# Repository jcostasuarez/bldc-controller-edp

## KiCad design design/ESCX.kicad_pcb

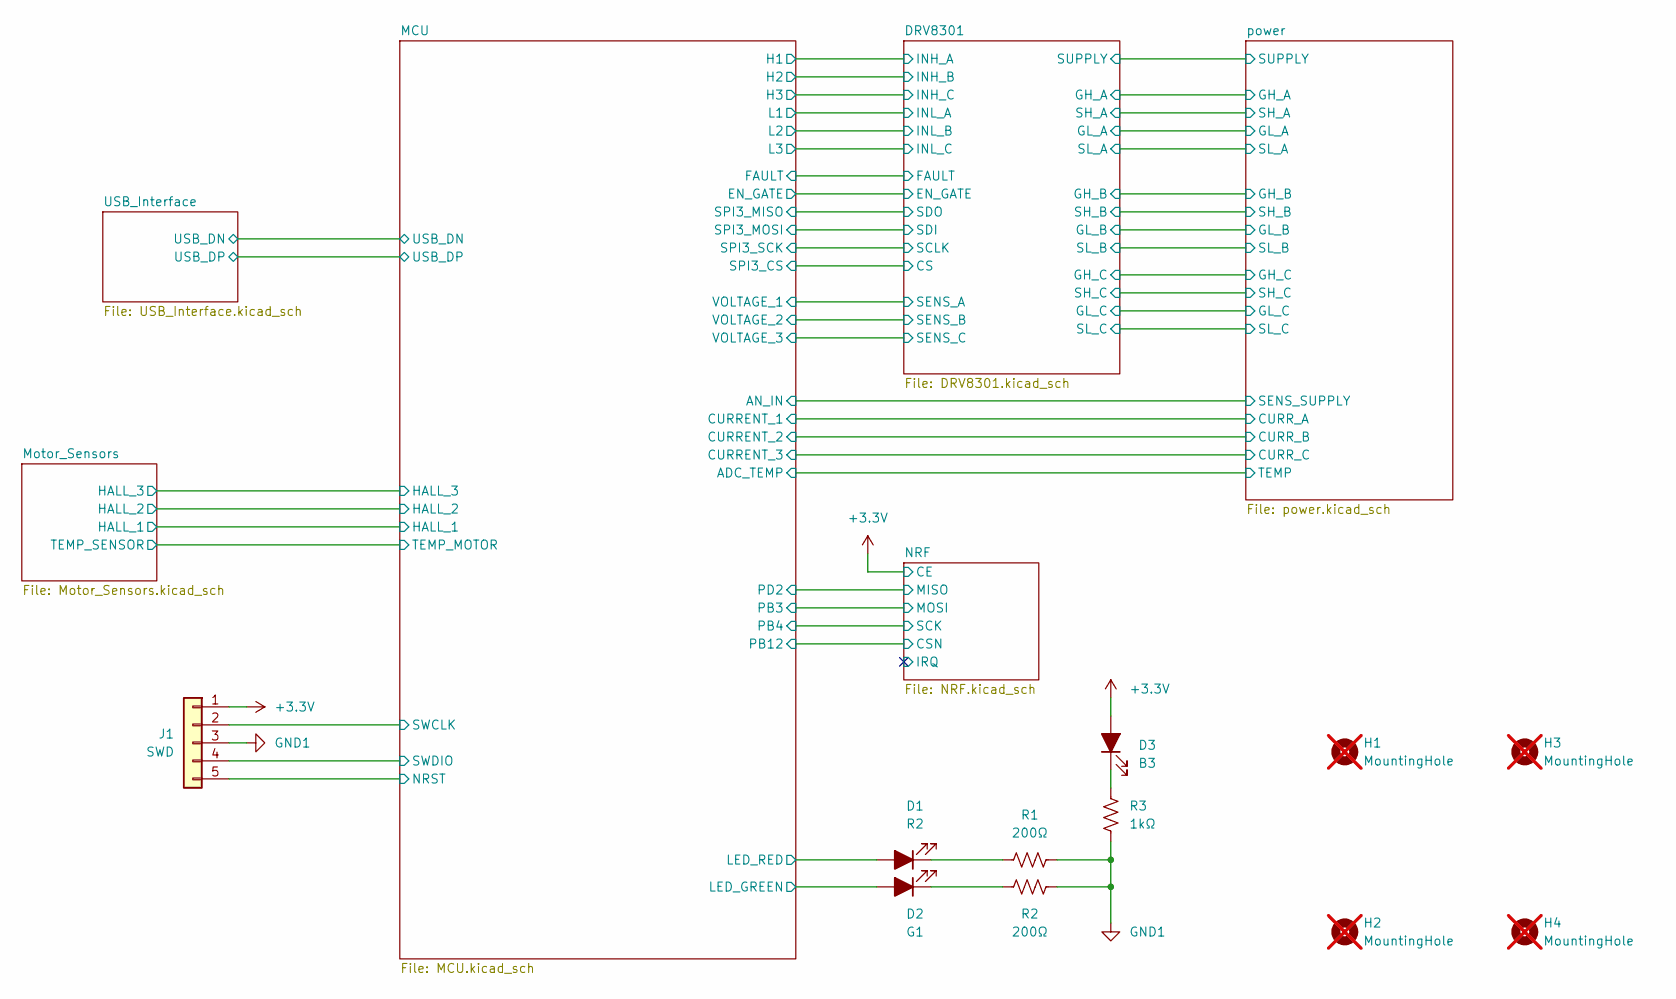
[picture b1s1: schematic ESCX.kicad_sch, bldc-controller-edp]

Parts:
D1: R2; LED_0603_1608Metric; LCSC C2286
D2: G1; LED_0603_1608Metric; LCSC C2286
D3: B3; LED_0603_1608Metric; LCSC C2286
H1, H2, H3, H4: MountingHole; MountingHole_2.7mm_M2.5; not fitted
J1: SWD; PinHeader_1x05_P2.54mm_Vertical; LCSC C6332198
R1, R2: 200Ω; R_0603_1608Metric; LCSC C8218
R3: 1kΩ; R_0603_1608Metric; LCSC C21190

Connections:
+3.3V: D3.2 (A), J1.1; also elsewhere on the board
/MCU/LED_GREEN: D2.2 (A); also elsewhere on the board
/MCU/LED_RED: D1.2 (A); also elsewhere on the board
/MCU/NRST: J1.5; also elsewhere on the board
/MCU/SWCLK: J1.2; also elsewhere on the board
/MCU/SWDIO: J1.4; also elsewhere on the board
GND1: J1.3, R1.2, R2.2, R3.1; also elsewhere on the board
unnamed: D1.1 (K), R1.1
unnamed: D2.1 (K), R2.1
unnamed: D3.1 (K), R3.2

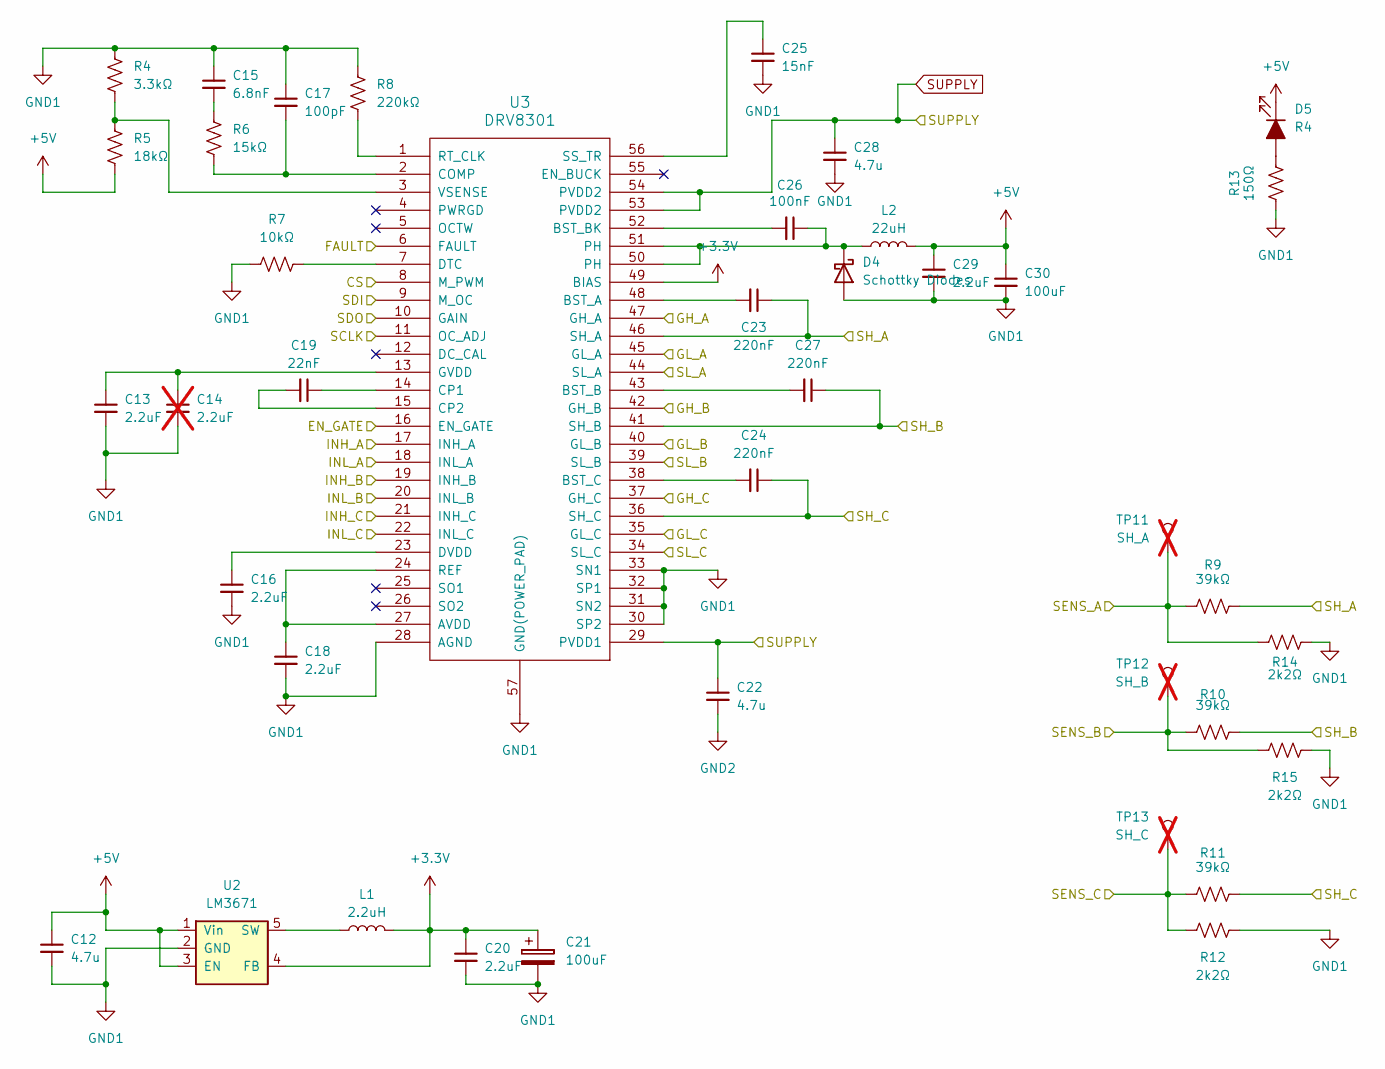
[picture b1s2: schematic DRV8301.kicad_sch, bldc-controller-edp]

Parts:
C12: 4.7u; C_0603_1608Metric; LCSC C19666
C13, C16, C18, C20, C29: 2.2uF; C_0603_1608Metric; LCSC C23630
C14: 2.2uF; C_0603_1608Metric; not fitted
C15: 6.8nF; C_0603_1608Metric; LCSC C1631
C17: 100pF; C_0603_1608Metric; LCSC C14858
C19: 22nF; C_0603_1608Metric; LCSC C21122
C21, C30: 100uF; C_1206_3216Metric; LCSC C15008
C22, C28: 4.7u; C_1210_3225Metric; LCSC C337978
C23, C24, C27: 220nF; C_0603_1608Metric; LCSC C21120
C25: 15nF; C_0603_1608Metric; LCSC C113809
C26: 100nF; C_0603_1608Metric; LCSC C14663
D4: Schottky Diodes; D_SMA; LCSC C22452
D5: R4; LED_0603_1608Metric; LCSC C2286
L1: 2.2uH; L_0603_1608Metric; LCSC C18221249
L2: 22uH; L_0603_1608Metric_Pad1.05x0.95mm_HandSolder; LCSC C6808015
R4: 3.3kΩ; R_0603_1608Metric; LCSC C22978
R5: 18kΩ; R_0603_1608Metric; LCSC C25810
R6: 15kΩ; R_0603_1608Metric; LCSC C22809
R7: 10kΩ; R_0603_1608Metric; LCSC C25804
R8: 220kΩ; R_0603_1608Metric; LCSC C22961
R9, R10, R11: 39kΩ; R_0603_1608Metric; LCSC C23153
R12, R14, R15: 2k2Ω; R_0603_1608Metric; LCSC C4190
R13: 150Ω; R_0603_1608Metric; LCSC C22808
TP11: SH_A; PinHeader_1x01_P2.54mm_Vertical; not fitted
TP12: SH_B; PinHeader_1x01_P2.54mm_Vertical; not fitted
TP13: SH_C; PinHeader_1x01_P2.54mm_Vertical; not fitted
U2: LM3671; MF05A; LCSC C2650333
U3: DRV8301; HTSSOP-56-1EP_6.1x14mm_P0.5mm_EP3.61x6.35mm; LCSC C98969

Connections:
+3.3V: C20.1, C21.1, L1.2, U2.4 (FB), U3.49 (BIAS); also elsewhere on the board
+5V: C12.1, C29.1, C30.1, D5.1 (K), L2.2, R5.2, U2.1 (Vin), U2.3 (EN); also elsewhere on the board
/DRV8301/CS: U3.8 (M_PWM); also elsewhere on the board
/DRV8301/EN_GATE: U3.16 (EN_GATE); also elsewhere on the board
/DRV8301/FAULT: U3.6 (FAULT); also elsewhere on the board
/DRV8301/GH_A: U3.47 (GH_A); also elsewhere on the board
/DRV8301/GH_B: U3.42 (GH_B); also elsewhere on the board
/DRV8301/GH_C: U3.37 (GH_C); also elsewhere on the board
/DRV8301/GL_A: U3.45 (GL_A); also elsewhere on the board
/DRV8301/GL_B: U3.40 (GL_B); also elsewhere on the board
/DRV8301/GL_C: U3.35 (GL_C); also elsewhere on the board
/DRV8301/INH_A: U3.17 (INH_A); also elsewhere on the board
/DRV8301/INH_B: U3.19 (INH_B); also elsewhere on the board
/DRV8301/INH_C: U3.21 (INH_C); also elsewhere on the board
/DRV8301/INL_A: U3.18 (INL_A); also elsewhere on the board
/DRV8301/INL_B: U3.20 (INL_B); also elsewhere on the board
/DRV8301/INL_C: U3.22 (INL_C); also elsewhere on the board
/DRV8301/SCLK: U3.11 (OC_ADJ); also elsewhere on the board
/DRV8301/SDI: U3.9 (M_OC); also elsewhere on the board
/DRV8301/SDO: U3.10 (GAIN); also elsewhere on the board
/DRV8301/SENS_A: R9.2, R14.2, TP11.1; also elsewhere on the board
/DRV8301/SENS_B: R10.2, R15.2, TP12.1; also elsewhere on the board
/DRV8301/SENS_C: R11.2, R12.2, TP13.1; also elsewhere on the board
/DRV8301/SH_A: C23.1, R9.1, U3.46 (SH_A); also elsewhere on the board
/DRV8301/SH_B: C27.1, R10.1, U3.41 (SH_B); also elsewhere on the board
/DRV8301/SH_C: C24.1, R11.1, U3.36 (SH_C); also elsewhere on the board
/DRV8301/SL_A: U3.44 (SL_A); also elsewhere on the board
/DRV8301/SL_B: U3.39 (SL_B); also elsewhere on the board
/DRV8301/SL_C: U3.34 (SL_C); also elsewhere on the board
GND1: C12.2, C13.2, C14.2, C15.1, C16.2, C17.1, C18.2, C20.2, C21.2, C25.2, C28.2, C29.2, C30.2, D4.2 (A), R4.1, R7.2, R8.1, R12.1, R13.2, R14.1, R15.1, U2.2 (GND), U3.28 (AGND), U3.30 (SP2), U3.31 (SN2), U3.32 (SP1), U3.33 (SN1), U3.57 (GND(POWER_PAD)); also elsewhere on the board
GND2: C22.2; also elsewhere on the board
unnamed: C15.2, R6.1
unnamed: C26.1, D4.1 (K), L2.1, U3.50 (PH), U3.51 (PH)
unnamed: D5.2 (A), R13.1
unnamed: L1.1, U2.5 (SW)
unnamed: C18.1, U3.24 (REF), U3.27 (AVDD)
unnamed: C23.2, U3.48 (BST_A)
unnamed: C27.2, U3.43 (BST_B)
unnamed: C26.2, U3.52 (BST_BK)
unnamed: C24.2, U3.38 (BST_C)
unnamed: C17.2, R6.2, U3.2 (COMP)
unnamed: C19.1, U3.14 (CP1)
unnamed: C19.2, U3.15 (CP2)
unnamed: R7.1, U3.7 (DTC)
unnamed: C16.1, U3.23 (DVDD)
unnamed: C13.1, C14.1, U3.13 (GVDD)
unnamed: R8.2, U3.1 (RT_CLK)
unnamed: C25.1, U3.56 (SS_TR)
unnamed: R4.2, R5.1, U3.3 (VSENSE)
SUPPLY: C22.1, C28.1, U3.29 (PVDD1), U3.53 (PVDD2), U3.54 (PVDD2); also elsewhere on the board

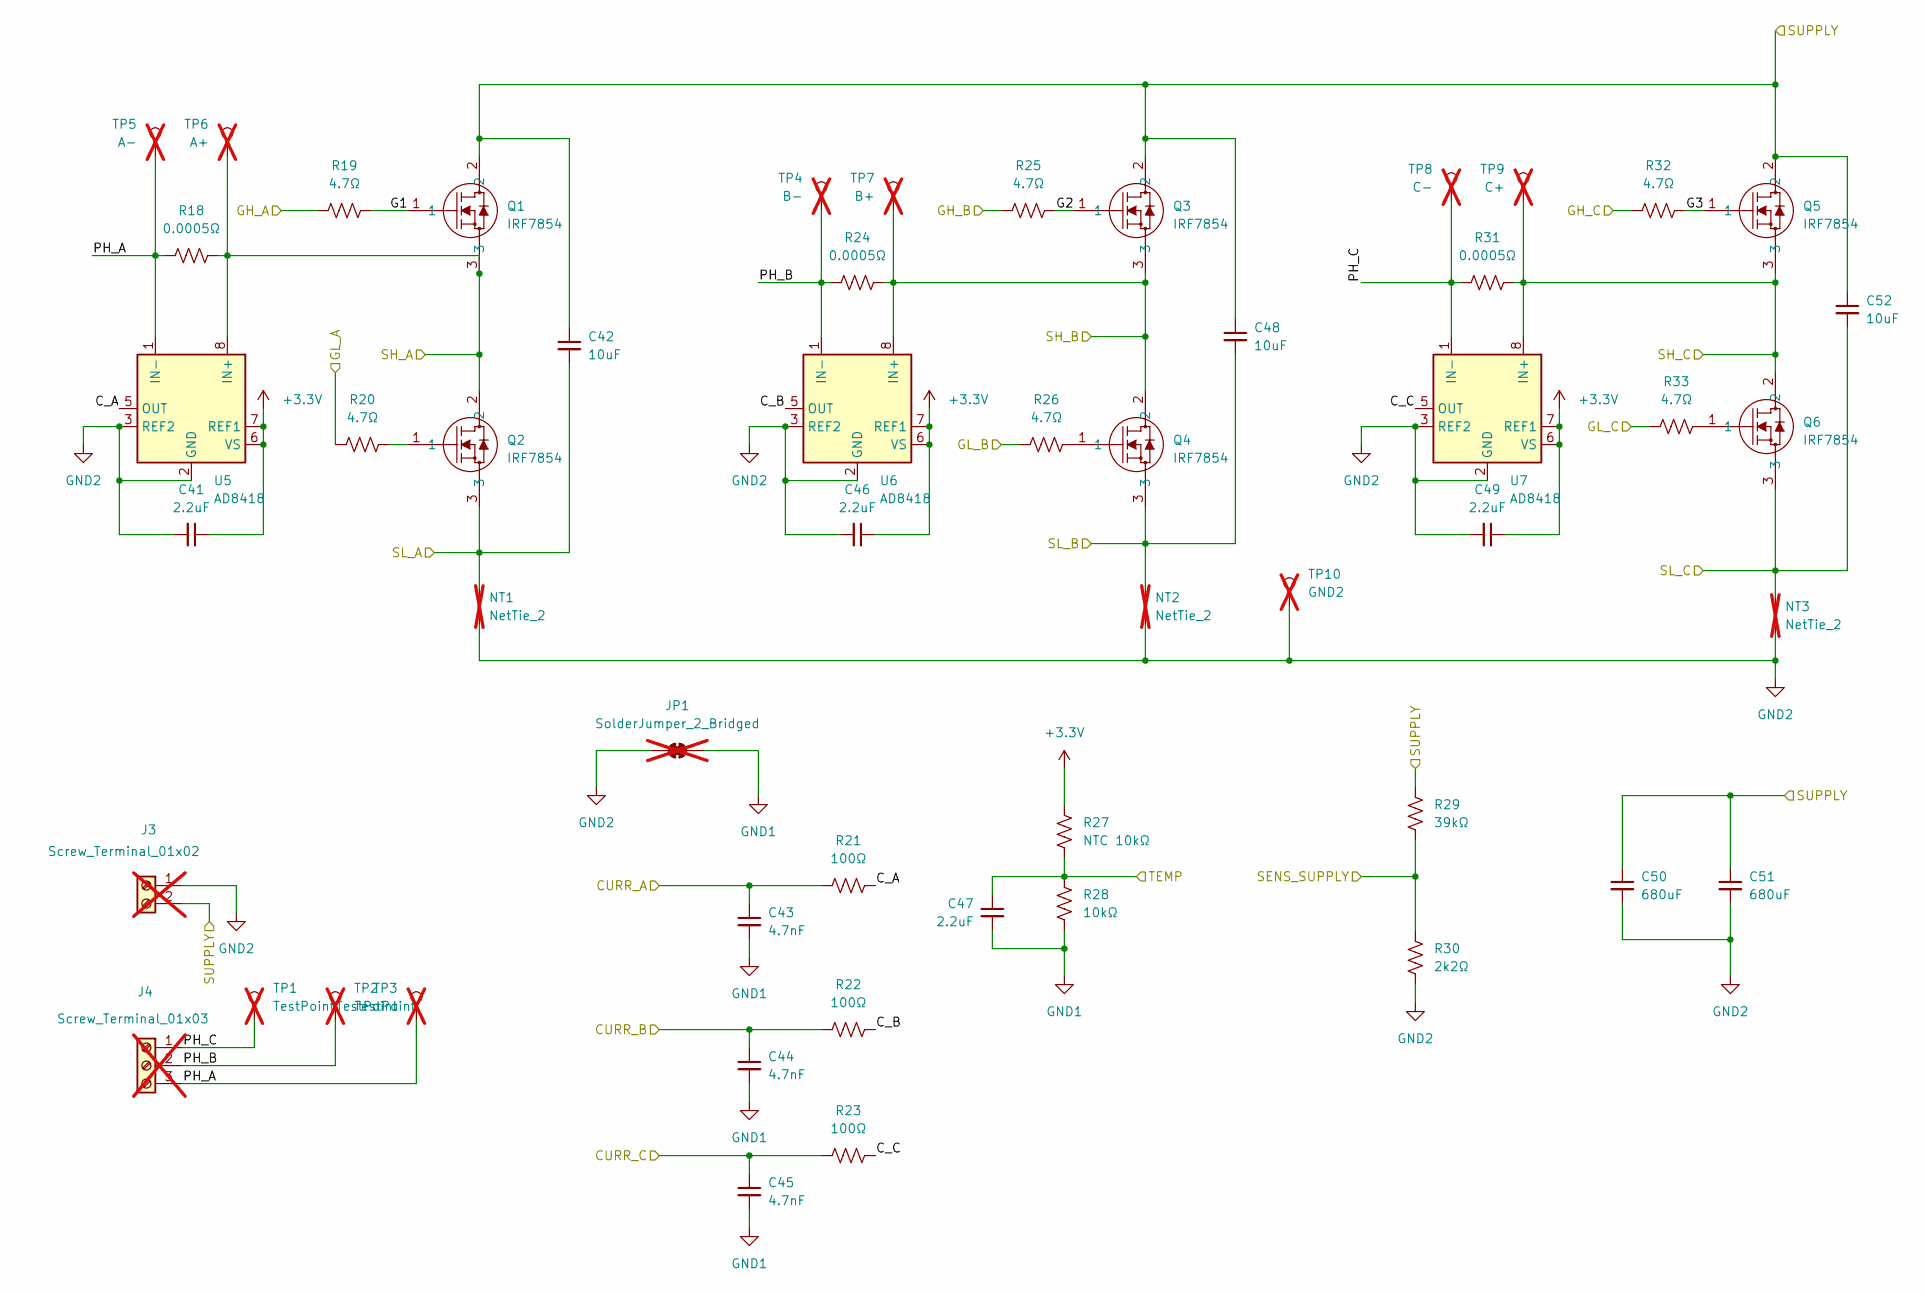
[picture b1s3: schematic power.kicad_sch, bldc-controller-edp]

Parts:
C41, C46, C47, C49: 2.2uF; C_0603_1608Metric; LCSC C23630
C42, C48, C52: 10uF; C_1210_3225Metric; LCSC C576517
C43, C44, C45: 4.7nF; C_0603_1608Metric; LCSC C53987
C50, C51: 680uF; C_Radial_D16.0mm_H25.0mm_P7.50mm; LCSC C407989
J3: Screw_Terminal_01x02; TerminalBlock_Phoenix_MKDS-1,5-2-5.08_1x02_P5.08mm_Horizont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; LCSC C480516; not fitted
J4: Screw_Terminal_01x03; TerminalBlock_Phoenix_MKDS-1,5-3-5.08_1x03_P5.08mm_Horizont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; LCSC C480520; not fitted
JP1: SolderJumper_2_Bridged; NetTie-2_SMD_Pad2.0mm; not fitted
NT1, NT2, NT3: NetTie_2; NetTie-2_SMD_Pad0.5mm; not fitted
Q1, Q2, Q3, Q4, Q5, Q6: IRF7854; SO-8_3.9x4.9mm_P1.27mm; LCSC C158109
R18, R24, R31: 0.0005Ω; R_2512_6332Metric; LCSC C3033267
R19, R20, R25, R26, R32, R33: 4.7Ω; R_0603_1608Metric; LCSC C23164
R21, R22, R23: 100Ω; R_0603_1608Metric; LCSC C22775
R27: NTC 10kΩ; R_0603_1608Metric; LCSC C524451
R28: 10kΩ; R_0603_1608Metric; LCSC C25804
R29: 39kΩ; R_0603_1608Metric; LCSC C23153
R30: 2k2Ω; R_0603_1608Metric; LCSC C4190
TP1, TP2, TP3: TestPoint; TestPoint_Pad_D4.0mm; not fitted
TP4: B-; PinHeader_1x01_P2.54mm_Vertical; not fitted
TP5: A-; PinHeader_1x01_P2.54mm_Vertical; not fitted
TP6: A+; PinHeader_1x01_P2.54mm_Vertical; not fitted
TP7: B+; PinHeader_1x01_P2.54mm_Vertical; not fitted
TP8: C-; PinHeader_1x01_P2.54mm_Vertical; not fitted
TP9: C+; PinHeader_1x01_P2.54mm_Vertical; not fitted
TP10: GND2; PinHeader_1x01_P2.54mm_Vertical; not fitted
U5, U6, U7: AD8418; R_8_ADI; LCSC C462197

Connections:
+3.3V: C41.1, C46.1, C49.1, R27.1, U5.6 (VS), U5.7 (REF1), U6.6 (VS), U6.7 (REF1), U7.6 (VS), U7.7 (REF1); also elsewhere on the board
/DRV8301/GH_A: R19.2; also elsewhere on the board
/DRV8301/GH_B: R25.2; also elsewhere on the board
/DRV8301/GH_C: R32.2; also elsewhere on the board
/DRV8301/GL_A: R20.2; also elsewhere on the board
/DRV8301/GL_B: R26.2; also elsewhere on the board
/DRV8301/GL_C: R33.2; also elsewhere on the board
/DRV8301/SH_A: Q1.3, Q2.2, R18.1, TP6.1, U5.8 (IN+); also elsewhere on the board
/DRV8301/SH_B: Q3.3, Q4.2, R24.1, TP7.1, U6.8 (IN+); also elsewhere on the board
/DRV8301/SH_C: Q5.3, Q6.2, R31.1, TP9.1, U7.8 (IN+); also elsewhere on the board
/DRV8301/SL_A: C42.2, NT1.2, Q2.3; also elsewhere on the board
/DRV8301/SL_B: C48.2, NT2.2, Q4.3; also elsewhere on the board
/DRV8301/SL_C: C52.2, NT3.2, Q6.3; also elsewhere on the board
/MCU/ADC_TEMP: C47.1, R27.2, R28.1; also elsewhere on the board
/MCU/AN_IN: R29.2, R30.2; also elsewhere on the board
/MCU/CURRENT_1: C43.1, R21.2; also elsewhere on the board
/MCU/CURRENT_2: C44.1, R22.2; also elsewhere on the board
/MCU/CURRENT_3: C45.1, R23.2; also elsewhere on the board
/power/C_A: R21.1, U5.5 (OUT)
/power/C_B: R22.1, U6.5 (OUT)
/power/C_C: R23.1, U7.5 (OUT)
/power/G1: Q1.1, R19.1
/power/G2: Q3.1, R25.1
/power/G3: Q5.1, R32.1
/power/PH_A: J4.3, R18.2, TP3.1, TP5.1, U5.1 (IN-)
/power/PH_B: J4.2, R24.2, TP2.1, TP4.1, U6.1 (IN-)
/power/PH_C: J4.1, R31.2, TP1.1, TP8.1, U7.1 (IN-)
GND1: C43.2, C44.2, C45.2, C47.2, JP1.2 (B), R28.2; also elsewhere on the board
GND2: C41.2, C46.2, C49.2, C50.2, C51.2, J3.1, JP1.1 (A), NT1.1, NT2.1, NT3.1, R30.1, TP10.1, U5.2 (GND), U5.3 (REF2), U6.2 (GND), U6.3 (REF2), U7.2 (GND), U7.3 (REF2); also elsewhere on the board
unnamed: Q2.1, R20.1
unnamed: Q4.1, R26.1
unnamed: Q6.1, R33.1
SUPPLY: C42.1, C48.1, C50.1, C51.1, C52.1, J3.2, Q1.2, Q3.2, Q5.2, R29.1; also elsewhere on the board

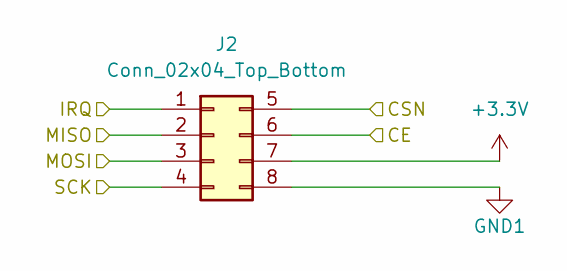
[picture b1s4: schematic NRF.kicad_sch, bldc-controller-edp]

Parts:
J2: Conn_02x04_Top_Bottom; PinHeader_2x04_P2.54mm_Vertical

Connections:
+3.3V: J2.6, J2.7; also elsewhere on the board
/MCU/PB3: J2.3; also elsewhere on the board
/MCU/PB4: J2.4; also elsewhere on the board
/MCU/PB12: J2.5; also elsewhere on the board
/MCU/PD2: J2.2; also elsewhere on the board
/NRF/IRQ: J2.1
GND1: J2.8; also elsewhere on the board

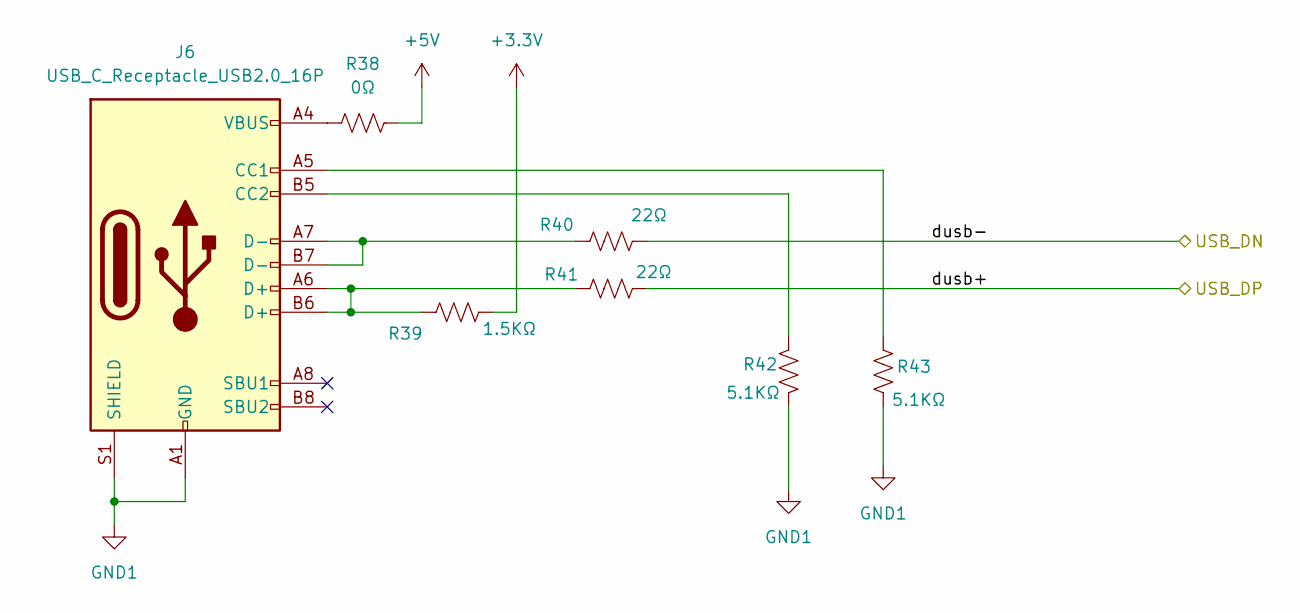
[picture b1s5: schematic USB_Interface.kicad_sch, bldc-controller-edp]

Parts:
J6: USB_C_Receptacle_USB2.0_16P; USB-SHOUHAN-TYPE-C16PIN; LCSC C393939
R38: 0Ω; R_0603_1608Metric; LCSC C21189
R39: 1.5KΩ; R_0603_1608Metric; LCSC C22843
R40, R41: 22Ω; R_0603_1608Metric; LCSC C23345
R42, R43: 5.1KΩ; R_0603_1608Metric; LCSC C23186

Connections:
+3.3V: R39.1; also elsewhere on the board
+5V: R38.1; also elsewhere on the board
/USB_Interface/dusb+: R41.1; also elsewhere on the board
/USB_Interface/dusb-: R40.1; also elsewhere on the board
GND1: J6.A1 (GND), J6.A12 (GND), J6.B1 (GND), J6.B12 (GND), J6.S1 (SHIELD), R42.1, R43.1; also elsewhere on the board
unnamed: J6.A5 (CC1), R43.2
unnamed: J6.B5 (CC2), R42.2
unnamed: J6.A6 (D+), J6.B6 (D+), R39.2, R41.2
unnamed: J6.A7 (D-), J6.B7 (D-), R40.2
unnamed: J6.A4 (VBUS), J6.A9 (VBUS), J6.B4 (VBUS), J6.B9 (VBUS), R38.2

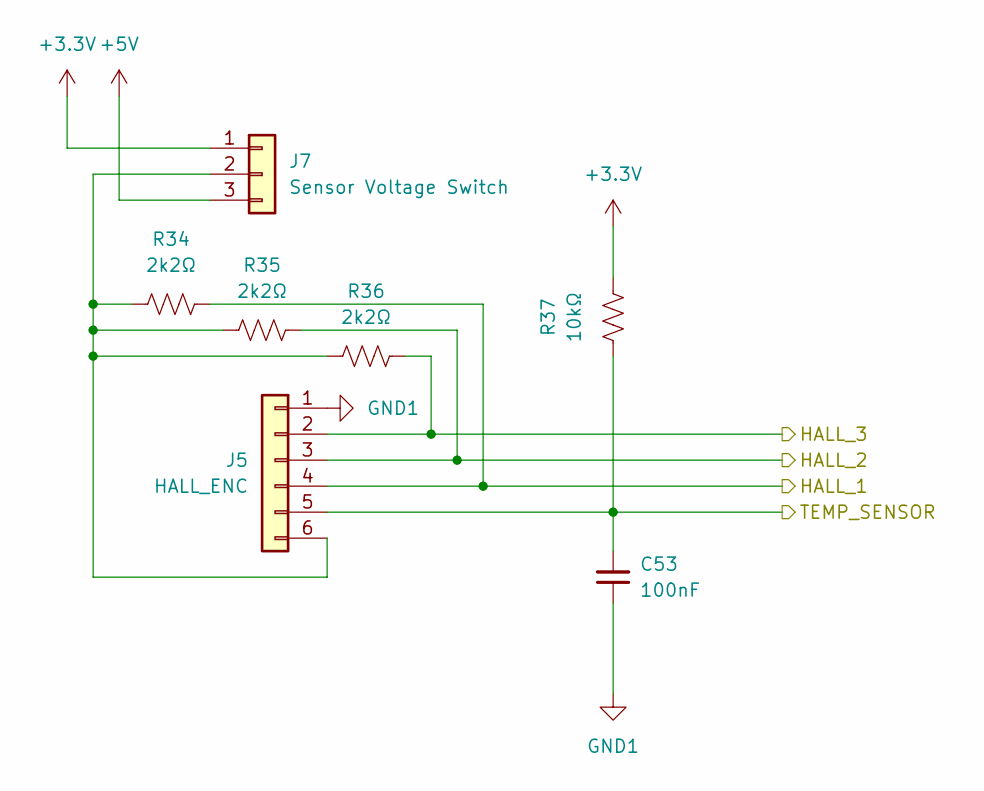
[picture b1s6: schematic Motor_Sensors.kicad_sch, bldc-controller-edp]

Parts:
C53: 100nF; C_0603_1608Metric; LCSC C14663
J5: HALL_ENC; PinSocket_1x06_P2.54mm_Vertical; LCSC C144397
J7: Sensor Voltage Switch; PinHeader_1x03_P2.54mm_Vertical; LCSC C2937625
R34, R35, R36: 2k2Ω; R_0603_1608Metric; LCSC C4190
R37: 10kΩ; R_0603_1608Metric; LCSC C25804

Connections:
+3.3V: J7.1, R37.1; also elsewhere on the board
+5V: J7.3; also elsewhere on the board
/MCU/HALL_1: J5.4, R34.1; also elsewhere on the board
/MCU/HALL_2: J5.3, R35.1; also elsewhere on the board
/MCU/HALL_3: J5.2, R36.1; also elsewhere on the board
/MCU/TEMP_MOTOR: C53.2, J5.5, R37.2; also elsewhere on the board
GND1: C53.1, J5.1; also elsewhere on the board
unnamed: J5.6, J7.2, R34.2, R35.2, R36.2

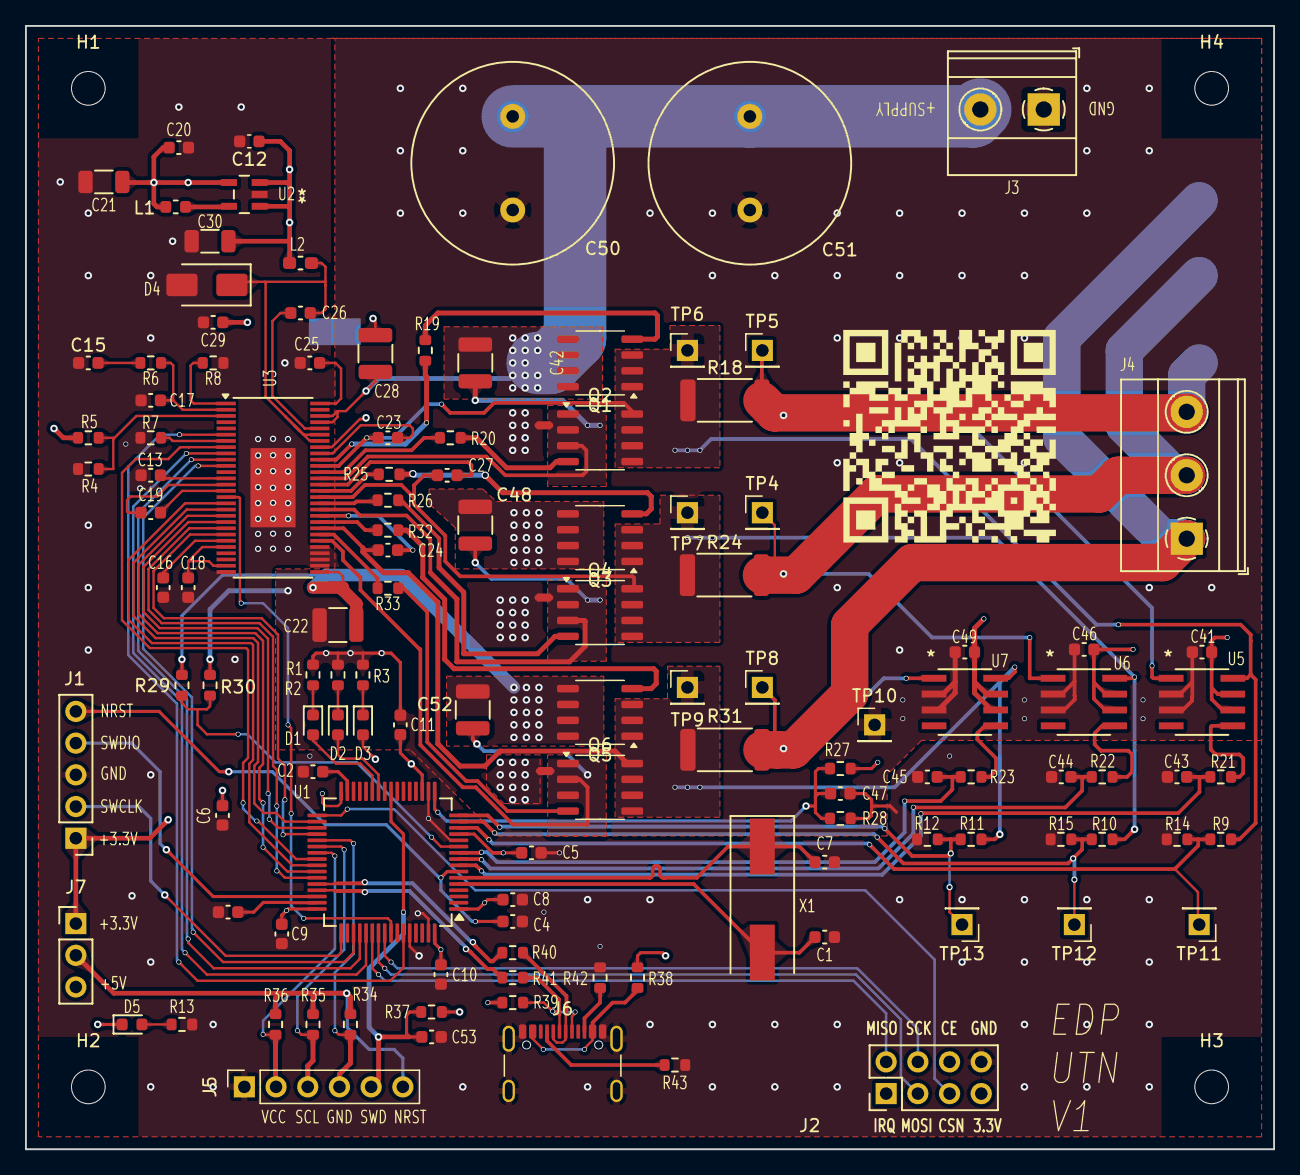
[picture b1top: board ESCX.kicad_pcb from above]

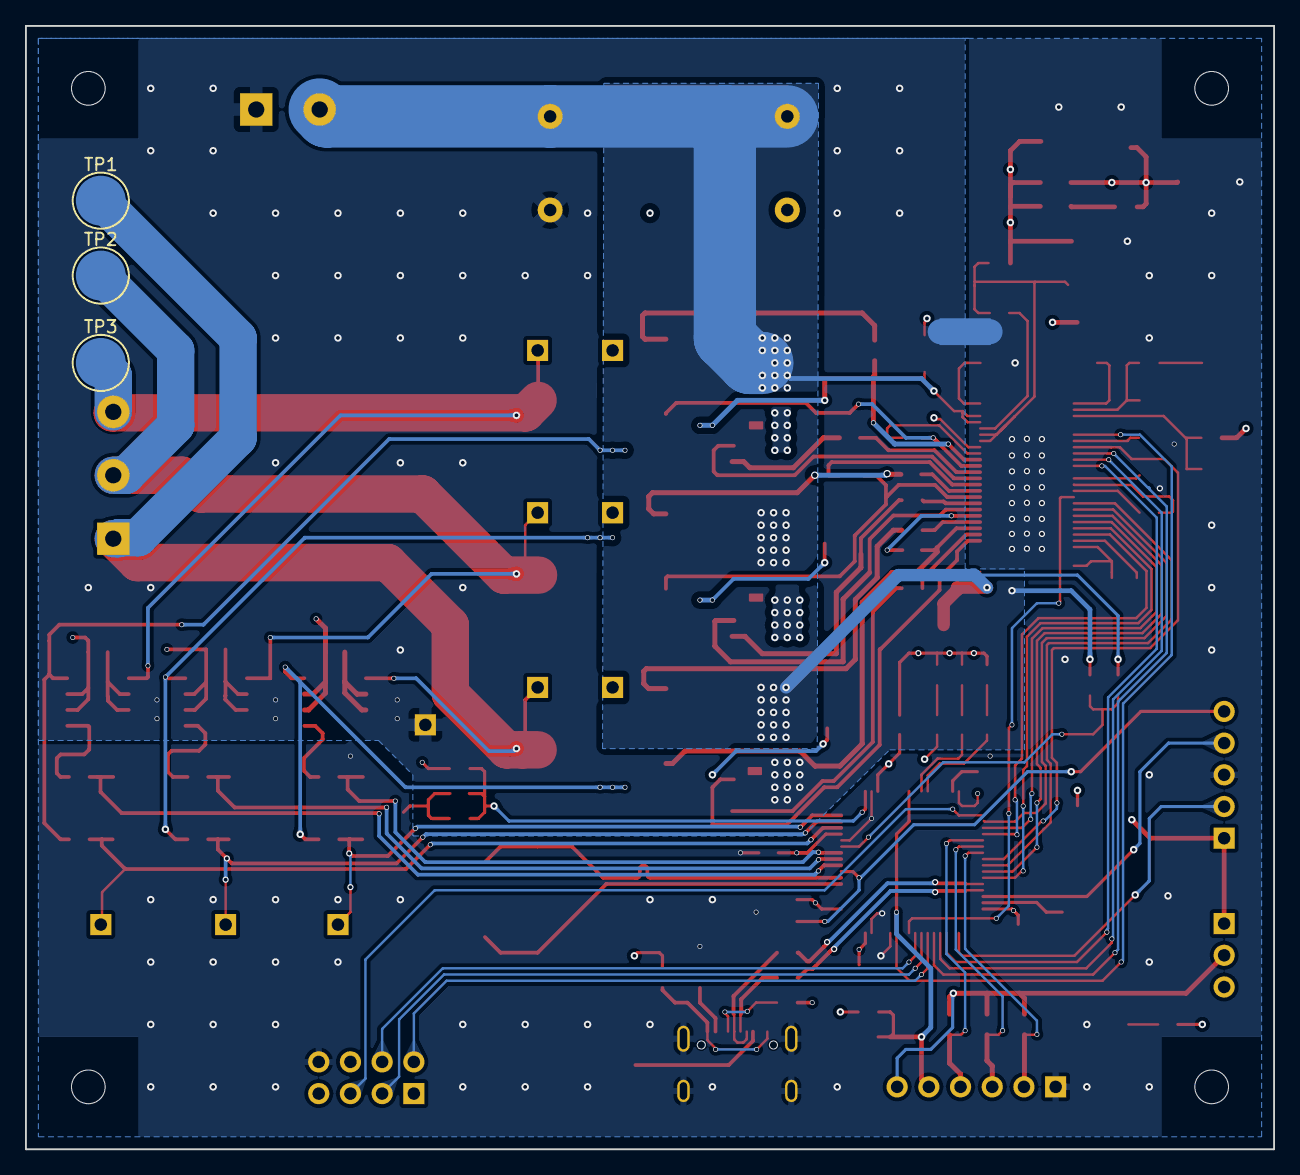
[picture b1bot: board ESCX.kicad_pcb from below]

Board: 4 copper layers, 100.0 x 90.0 mm, 131 parts (4 on the bottom side), 95 nets.

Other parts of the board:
C1, C7: 15pF; C_0603_1608Metric
C2, C3, C5, C6, C8, C9, C10, C11: 2.2uF; C_0603_1608Metric
C4: 100nF; C_0603_1608Metric
U1: STM32F40X_LQFP64; LQFP-64_10x10mm_P0.5mm
X1: 8MHz; Crystal_SMD_HC49-SD

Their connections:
+3.3V: C5.1, C6.1, C8.1, C9.1, C10.1, C11.1, U1.1 (VBAT), U1.13 (VDDA), U1.19 (VDD), U1.32 (VDD), U1.48 (VDD), U1.64 (VDD); also elsewhere on the board
/DRV8301/CS: U1.40 (PC9); also elsewhere on the board
/DRV8301/EN_GATE: U1.57 (PB5); also elsewhere on the board
/DRV8301/FAULT: U1.59 (PB7); also elsewhere on the board
/DRV8301/INH_A: U1.41 (PA8); also elsewhere on the board
/DRV8301/INH_B: U1.42 (PA9(OTG_FS_VBUS)); also elsewhere on the board
/DRV8301/INH_C: U1.43 (PA10); also elsewhere on the board
/DRV8301/INL_A: U1.34 (PB13(OTG_HS_VBUS)); also elsewhere on the board
/DRV8301/INL_B: U1.35 (PB14); also elsewhere on the board
/DRV8301/INL_C: U1.36 (PB15); also elsewhere on the board
/DRV8301/SCLK: U1.51 (PC10); also elsewhere on the board
/DRV8301/SDI: U1.53 (PC12); also elsewhere on the board
/DRV8301/SDO: U1.52 (PC11); also elsewhere on the board
/DRV8301/SENS_A: U1.14 (PA0(ADC123_IN0/WKUP)); also elsewhere on the board
/DRV8301/SENS_B: U1.15 (PA1(ADC123_IN1)); also elsewhere on the board
/DRV8301/SENS_C: U1.16 (PA2(ADC123_IN2)); also elsewhere on the board
/MCU/ADC_TEMP: U1.17 (PA3(ADC123_IN3)); also elsewhere on the board
/MCU/AN_IN: U1.11 (PC3(ADC123_IN13)); also elsewhere on the board
/MCU/CURRENT_1: U1.8 (PC0(ADC123_IN10)); also elsewhere on the board
/MCU/CURRENT_2: U1.9 (PC1(ADC123_IN11)); also elsewhere on the board
/MCU/CURRENT_3: U1.10 (PC2(ADC123_IN12)); also elsewhere on the board
/MCU/HALL_1: U1.37 (PC6); also elsewhere on the board
/MCU/HALL_2: U1.38 (PC7); also elsewhere on the board
/MCU/HALL_3: U1.39 (PC8); also elsewhere on the board
/MCU/LED_GREEN: U1.26 (PB0(ADC12_IN8)); also elsewhere on the board
/MCU/LED_RED: U1.27 (PB1(ADC12_IN9)); also elsewhere on the board
/MCU/NRST: C4.1, U1.7 (NRST); also elsewhere on the board
/MCU/PB3: U1.55 (PB3(JTDO/TRACESWO)); also elsewhere on the board
/MCU/PB4: U1.56 (PB4(NJTRST)); also elsewhere on the board
/MCU/PB12: U1.33 (PB12); also elsewhere on the board
/MCU/PD2: U1.54 (PD2); also elsewhere on the board
/MCU/SWCLK: U1.49 (PA14(JTCK-SWCLK)); also elsewhere on the board
/MCU/SWDIO: U1.46 (PA13(JTMS-SWDIO)); also elsewhere on the board
/MCU/TEMP_MOTOR: U1.24 (PC4(ADC12_IN14)); also elsewhere on the board
/USB_Interface/dusb+: U1.45 (PA12); also elsewhere on the board
/USB_Interface/dusb-: U1.44 (PA11); also elsewhere on the board
GND1: C1.1, C2.1, C3.1, C4.2, C5.2, C6.2, C7.1, C8.2, C9.2, C10.2, C11.2, U1.12 (VSSA), U1.18 (VSS), U1.60 (BOOT0(VPP)), U1.63 (VSS); also elsewhere on the board
unnamed: C1.2, U1.5 (PH0-OSC_IN), X1.2
unnamed: C7.2, U1.6 (PH1-OSC_OUT), X1.1
unnamed: C2.2, U1.31 (VCAP1)
unnamed: C3.2, U1.47 (VCAP2)

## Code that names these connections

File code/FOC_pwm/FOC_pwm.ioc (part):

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Mcu.Name=STM32F401R(B-C)Tx
Mcu.Package=LQFP64
Mcu.UserName=STM32F401RCTx
PA0-WKUP.GPIOParameters=GPIO_Label
PA0-WKUP.GPIO_Label=VOLTAGE_1
PA0-WKUP.Signal=ADCx_IN0
PA1.GPIOParameters=GPIO_Label
PA1.GPIO_Label=VOLTAGE_2
PA1.Signal=ADCx_IN1
PA10.GPIOParameters=GPIO_Speed,GPIO_PuPd
PA10.GPIO_PuPd=GPIO_NOPULL
PA10.GPIO_Speed=GPIO_SPEED_FREQ_LOW
PA10.Signal=S_TIM1_CH3
PA13.Mode=Serial_Wire
PA13.Signal=SYS_JTMS-SWDIO
PA14.Mode=Serial_Wire
PA14.Signal=SYS_JTCK-SWCLK
PA2.GPIOParameters=GPIO_Label
PA2.GPIO_Label=VOLTAGE_3
PA2.Signal=ADCx_IN2
PA3.GPIOParameters=GPIO_Label
PA3.GPIO_Label=ADC_TEMP
PA3.Signal=ADCx_IN3
PA8.GPIOParameters=GPIO_Speed,GPIO_PuPd
PA8.GPIO_PuPd=GPIO_NOPULL
PA8.GPIO_Speed=GPIO_SPEED_FREQ_LOW
PA8.Signal=S_TIM1_CH1
PA9.GPIOParameters=GPIO_Speed,GPIO_PuPd
PA9.GPIO_PuPd=GPIO_NOPULL
PA9.GPIO_Speed=GPIO_SPEED_FREQ_LOW
PA9.Signal=S_TIM1_CH2
PB0.GPIOParameters=GPIO_PuPd,GPIO_Label
PB0.GPIO_Label=LED_G
PB0.GPIO_PuPd=GPIO_NOPULL
PB0.Signal=GPIO_Output
PB1.GPIOParameters=GPIO_Label
PB1.GPIO_Label=LED_R
PB1.Signal=GPIO_Output
PB13.GPIOParameters=GPIO_Speed,GPIO_PuPd
PB13.GPIO_PuPd=GPIO_NOPULL
PB13.GPIO_Speed=GPIO_SPEED_FREQ_LOW
PB13.Mode=PWM Generation1 CH1 CH1N
PB13.Signal=TIM1_CH1N
PB14.GPIOParameters=GPIO_Speed,GPIO_PuPd
PB14.GPIO_PuPd=GPIO_NOPULL
PB14.GPIO_Speed=GPIO_SPEED_FREQ_LOW
PB14.Mode=PWM Generation2 CH2 CH2N
PB14.Signal=TIM1_CH2N
PB15.GPIOParameters=GPIO_Speed,GPIO_PuPd
PB15.GPIO_PuPd=GPIO_NOPULL
PB15.GPIO_Speed=GPIO_SPEED_FREQ_LOW
PB15.Mode=PWM Generation3 CH3 CH3N
PB15.Signal=TIM1_CH3N
PB3.GPIOParameters=GPIO_Speed,PinState,GPIO_Label
PB3.GPIO_Label=UART_TX
PB3.GPIO_Speed=GPIO_SPEED_FREQ_VERY_HIGH
PB3.PinState=GPIO_PIN_SET
PB3.Signal=GPIO_Output
PB5.GPIOParameters=PinState,GPIO_Label
PB5.GPIO_Label=EN_GATE
PB5.PinState=GPIO_PIN_RESET
PB5.Signal=GPIO_Output
PB7.GPIOParameters=GPIO_PuPd,GPIO_Label,GPIO_ModeDefaultEXTI
PB7.GPIO_Label=nFAULT
PB7.GPIO_ModeDefaultEXTI=GPIO_MODE_IT_RISING_FALLING
PB7.GPIO_PuPd=GPIO_PULLUP
PB7.Signal=GPXTI7
PC0.GPIOParameters=GPIO_Label
PC0.GPIO_Label=CURRENT_1
PC0.Signal=ADCx_IN10
PC1.GPIOParameters=GPIO_Label
PC1.GPIO_Label=CURRENT_2
PC1.Signal=ADCx_IN11
PC10.GPIOParameters=GPIO_Speed,GPIO_Label
PC10.GPIO_Label=SPI3_SCK
PC10.GPIO_Speed=GPIO_SPEED_FREQ_VERY_HIGH
PC10.Signal=GPIO_Output
PC11.GPIOParameters=GPIO_Label
PC11.GPIO_Label=SPI3_MISO
PC11.Signal=GPIO_Input
PC12.GPIOParameters=GPIO_Speed,GPIO_Label
PC12.GPIO_Label=SPI3_MOSI
PC12.GPIO_Speed=GPIO_SPEED_FREQ_VERY_HIGH
PC12.Signal=GPIO_Output
PC2.GPIOParameters=GPIO_Label
PC2.GPIO_Label=CURRENT_3
PC2.Signal=ADCx_IN12
PC3.GPIOParameters=GPIO_Label
PC3.GPIO_Label=VOLTAGE_SUPPLY
PC3.Signal=ADCx_IN13
PC4.GPIOParameters=GPIO_Label
PC4.GPIO_Label=TEMP_MOTOR
PC4.Signal=ADCx_IN14
PC6.GPIOParameters=GPIO_PuPd,GPIO_Label
PC6.GPIO_Label=HALL1
PC6.GPIO_PuPd=GPIO_PULLUP
PC6.Signal=GPIO_Input
PC7.GPIOParameters=GPIO_PuPd,GPIO_Label
PC7.GPIO_Label=HALL2
PC7.GPIO_PuPd=GPIO_PULLUP
PC7.Signal=GPIO_Input
PC8.GPIOParameters=GPIO_PuPd,GPIO_Label
PC8.GPIO_Label=HALL3
PC8.GPIO_PuPd=GPIO_PULLUP
PC8.Signal=GPIO_Input
PC9.GPIOParameters=GPIO_Speed,GPIO_Label
PC9.GPIO_Label=SPI3_CS
PC9.GPIO_Speed=GPIO_SPEED_FREQ_VERY_HIGH
PC9.Signal=GPIO_Output
PD2.GPIOParameters=GPIO_PuPd,GPIO_Label,GPIO_ModeDefaultEXTI
PD2.GPIO_Label=UART_RX
PD2.GPIO_ModeDefaultEXTI=GPIO_MODE_IT_FALLING
PD2.GPIO_PuPd=GPIO_PULLUP
PD2.Signal=GPXTI2
PH0\ -\ OSC_IN.Mode=HSE-External-Oscillator
PH0\ -\ OSC_IN.Signal=RCC_OSC_IN
PH1\ -\ OSC_OUT.Mode=HSE-External-Oscillator
PH1\ -\ OSC_OUT.Signal=RCC_OSC_OUT
RCC.HSE_VALUE=8000000
RCC.SYSCLKFreq_VALUE=16000000
board=custom

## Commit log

2024-08-19 Update README.md
    Eliminado del contenido del archivo readmi.md
2024-08-19 Importado bibliotecas de símbolos
    Bibliotecas importadas
2024-08-19 Eliminado módulo CAN, agregado módulo bluetooth
    Eliminado de hoja CAN, añadido de módulo bluetooth
2024-08-20 Actualización VESC6.4
    Actualización a esquemáticos de VESC6.4, faltan asignación de huellas y descripción a cada elemento.
2024-08-20 Impresión de esquemático en pdf
    Impresión de la versión del esquemático en la carpeta /pdf
2024-08-20 Pequeños cambios
    Se sacaron y se marcaron como NC:
    * CAN_TX y CAN_RX (no se usa CAN).
    * SERVO (no vamos a manejar servomotores).
    * ADC_15, MISO_ADC_EXT, TX_SCL_MOSI, RX_SDA_NSS, SCK_ADC_EXT (sin ADC externo ni acelerómetro).
2024-08-20 Agregado ibom
    Pequeños cambios en el esquemático y agregado de ibom
2024-08-22 Cambios en el esquemático
    - Cambio de Vcc por +3.3V
    - Agregado de hoja para desarrollar la entrada de tensión alterna
2024-08-23 Agregado de footprints
2024-08-23 Commit antes del merge
2024-08-25 Agrego MFR.Part # a capacitores
2024-08-27 Agregue Manufacturer Product Numbers
2024-08-27 agrego footprint para oscilador
2024-08-28 Cambie a USB C
2024-08-28 Agregue Manufacturer Product Number
2024-08-29 Ordenado del esquemático
    - Cambios en los capacitores del oscilador
    - Mejora de los esquemáticos, encapsulado la interfáz usb y los sensores del motor
2024-08-29 Pequeños cambios
    Pequeños cambios, eliminado de carpeta BLDC
2024-08-29 Gitignore
    Agregado de archivos .zip
2024-08-29 Deleted .zip
    Eliminado de archivos .zip
2024-08-29 Annotate
    Update anotation
2024-08-29 Pequeños cambios
    Pequeños cambios en esquemático
2024-09-01 Agrego MFR# de conectores
2024-09-06 Empiezo a ubicar componentes en PCB
2024-09-10 Ubico componentes de USB
2024-09-10 inicio ruteo de MCU y USB
2024-09-16 Continue rooteo del MCU y modulo BT
2024-09-17 Continuacion de Rooteo
2024-09-18 Ruteo del driver y ubicacion de MOSFETs
2024-09-18 Complete ruteo, menos plano GND2
2024-09-18 Finalizado de ruteo de pcb
2024-09-26 Reubicacion de capacitores de entrada y mejora de ruteo
2024-09-27 Correccion de errores
2024-09-28 cambio en el plano Supply y reubicacion de componentes
2024-09-28 Re-ruteo de etapa de potencia
2024-09-30 Agrego pad termico en el Bottom layer
2024-09-30 aumento de ancho de pistas de alimentacion del driver
2024-09-30 cambie jumpers de GND1 - GND2 por pistas
2024-09-30 cambios en el esquematico
2024-10-02 Arreglos y cambios
    Cambios en ruteos, dimensión de la placa, tamaño de las vías, parámetros de diseño jlcpb (constraints). Agregado de pad térmico de transistores, duplicado de capa inferior y superior para mejor disip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
2024-10-02 Cambios en clearance de pad térmico bot
    Cambio de clearance de 0.8mm a 0.4mm
2024-10-03 Simplificaciones
    Pequeños cambios, ruteo mas prolijo, despejado del plano de tensión, agregado de la unión de tierras
2024-10-03 Cambios pequeños
    Agregado de pads de soldado, mejora de rooteo pequeña
2024-10-03 Guardado de esquemático
    Cambios en footprints de esquemático, agregado de footrpints de testpoints
2024-10-04 Ultimo push antes de rotar el driver
    Se pidió rotar el driver.
2024-10-05 Rotado del driver
    Rotado del driver, cambiado de capacitores, disipación de transistores, cambiado de capacitores de semi puentes.
2024-10-06 leds ruteados en la B. Layer
2024-10-06 cambios en ruteo
2024-10-06 ruteo completo
2024-10-06 ruteo de USB
2024-10-07 correccion en el esquematico
2024-10-07 Cambios en posicion de capacitores de transistores
    Tambien agregado de vias de tierra
2024-10-07 Cambios a constraints
    Cambios de constraints de ancho mínimo para pasar DRC
2024-10-13 Cambios en numero de partes
    Updeteados algunos numeros de JLCPCB
2024-10-14 Agregue LCSC Part #
2024-10-14 Agregue LCSC Part # a algunas resistencias
2024-10-15 Correccion de algunos DRC
2024-10-15 Correccion de DRC
2024-10-15 Agrego # de los cristales
2024-10-15 reubicacion de designadores de Silkscreen
2024-10-15 Agrego texto con +supply
2024-10-15 Cambio de switch de tension del sensor por jumper
2024-10-17 Abaratando costos
    Cambios en numeros de jlcpcb, pasados a componentes básicos
2024-10-17 cambie resistencias a basic
2024-10-18 Sacado de NRF
    Sacado de NRF, re-hecho constraints
2024-10-18 Pequeños cambios finales
    Agregado de test points, cambiado de algunos footprints, agregado de QR
2024-10-18 Guardado esquemático
    Faltó guardar
2024-10-20 cambios en la BOM
2024-10-24 Cambios
    Actualizado footprint de USB, cambio de capacitor de feedback por uno básico, pequeños cambios en la ubicación de los footprints.
2024-12-02 add ST projects
2024-12-05 Agregado código con pwm
2024-12-05 nfault triggered on driver
2024-12-06 Uncompleted bit bang from bedder
2024-12-06 remove metadata
2024-12-06 Fix issues with bedder copy
2024-12-06 Agregado de Led y Debug
    Agregado de bibliotecas Led y Debug para manejo de comunicaciones. La biblioteca Debug, utiliza el Led Rojo.
2024-12-06 Agregado de bibliotecas del ADC
    Agregado de bibliotecas para usar ADC. Todavía no esta funcional las conversiones para leer valores reales.
2024-12-06 Funciones del ADC corregidas
    Corrección de las funciones del ADC, ahora cada una mide los valores reales. excepcion de get temp motor, porque se desconocen los valores del sensor de temperatura del motor.
2024-12-06 Update drv8301.c
    Agregado de funciones de debug a la biblioteca, ahora el led rojo indicara una falla en la transmision o recepción de los datos
2024-12-06 working pwm signal
2024-12-06 Andando
2024-12-09 Add bit bang uart and speed control
2024-12-09 Fix speed sent not being a uint8_t
2024-12-09 Remove "times 8" in duty calculations
2024-12-09 Add anti embalamiento del duty
2024-12-12 Presentation day
